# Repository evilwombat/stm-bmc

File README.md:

# Summary

## What is bubble memory?
[Bubble memory](https://en.wikipedia.org/wiki/Bubble_memory]) is an archaic (yet super awesome) type of nonvolatile computer memory. It stores data as a pattern of magnetization on the surface of a crystal, in a manner loosely similar to a magnetic hard drive. The amazing thing about bubble memory is that despite being magnetic in nature, it uses **no moving parts**. Unlike a magnetic hard drive, the storage medium stays in place, but the *data* moves along its surface. This is accomplished through some magical properties of the [crystal](https://en.wikipedia.org/wiki/Gadolinium_gallium_garnet) involved. Bubble memory was a promising new storage technology in the 70s and 80s, due to (at the time) impressive densities, though it was ultimately replaced by cheaper and more reliable flash memories. 

## What is this project?
This is a controller for Bubble Memory modules made by Texas Instruments in the 1980s. I have brought this up using TIB S0004 memory modules. This is a reasonably functional controller, capable of reading, erasing, and writing data, though some of the analog circuitry could probably use some refinement. This was a quarantine project so I had to start with what I had at the time.

## Demo videos (click to play)

PCB version: http://www.youtube.com/watch?v=yxEgAI12R1k

PCB (with explanation): http://www.youtube.com/watch?v=7U3c4cfQvKs

Original, breadboarded version: http://www.youtube.com/watch?v=vP2biZnxT7Y

Honestly, I can't believe the breadboard version even worked cleanly enough for bringup. Notice the sense amplifier on a separate PCB.

## Implementation

Since bubble memory modules lack an internal controller, a fair amount of external circuitry is needed to produce the carefully-timed constant-current pulses needed to run them, and to amplify/process the output of the bubble detector. Historically, the timing of the control pulses was generated by a pile of logic circuits, or by a microsequencer. Later, both Intel and TI released some ICs to assist with this. Although today these are largely unobtanium, some documentation survives, including an [early design document](Research/DevelcoReport.pdf) that predates the existence of the integrated controller. The discrete-transistor implementation of the function pulse generator (and the associated timing information) found in this document is what made this project possible.

In modern times, the digital portion of such a controller can be reasonably implemented using a regular microcontroller, in this case, an STM32F103. The state machine and timing logic is handled entirely in firmware, but a fair amount of external circuitry is still needed to convert the logic-level signals into coil drive pulses and/or constant-current "function" pulses that are fed into the bubble module itself.

The STM32 firmware implements the following:
* Bubble function timing generator (Generate/Annihilate/Transfer)
* Coil drive timing generator
* Major/minor loop state machine
* Basic loop tests, for bringup/tuning of the analog circuit
* Block I/O layer (with CRC and trivial block redundancy)
* UI layer (LCD, fonts, graphics, rotary encoder)
* Bootloader to actually load code from the bubble memory and run it
* Proof-of-concept payload that can be loaded and booted
* [Morning Music](https://www.youtube.com/watch?v=tEueYGq2mT4) (obviously)

Although historical documentation exists, most of the detailed information pertains to an earlier prototype of TI bubble memory (TBM0101), one that was ultimately not commercialized. In the more widely-available parts (such as TIB0203 and the TIB-S0004 used here), some of the key operating parameters (such as drive cycle timings and function timings) have changed substantially. The correct parameters needed to be determined partly by trial and error, and partly by translating some old Russian datasheets relating to their knockoffs of TI's more modern bubble memory parts.

## Hardware Gallery

Assembled PCB version:

Schematic:

PCB layout:

First breadboarded version:

Close-up up of the breadboarded analog section. The amplifier circuit is too sensitive for breadboarding, and was built on a piece of perf-board. An alternate amplifier design would be less sensitive to minor variations in detector resistance, and hence would not need to many trimpots. But this design would be more sensitive to noise (which was much harder to control in a setup like this).

Some of the first bubbles!

## What's with the music and countdown?

Perhaps the best-known example of a bubble memory design is Konami's famous [Bubble System](https://en.wikipedia.org/wiki/Bubble_System) arcade platform.

In 1985, Konami released a number of arcade machines that used bubble memory (rather than silicon ROM) for game storage. When switched on, these machines spoke a voice-based countdown while the memory modules were heated to their operating temperature. Since bubble memory is read slowly and sequentially, the game residing within was first copied into RAM before it could be executed; the machine displayed an [on-screen countdown](https://www.youtube.com/watch?v=mbM_YPyVJBE&t=175s) (and played an accompanying melody) during this process. The system was ultimately a commercial failure, because the bubble memory was expensive and very sensitive to external magnetic fields; meanwhile, silicon-based storage was growing cheaper. The few games that used this system were eventually re-released on ROM, but some original bubble-based systems survive to this day. 

<b>Fun fact:</b> The melody that played during the loading countdown was called the Morning Music, because it played every morning when the arcade operator switched on the machine. It has been said that the boot process was a kind of special / unusual thing to see, and that people would show up bright and early to the arcade just to watch the machines boot (and to listen to the morning music).

> Written with [StackEdit](https://stackedit.io/).

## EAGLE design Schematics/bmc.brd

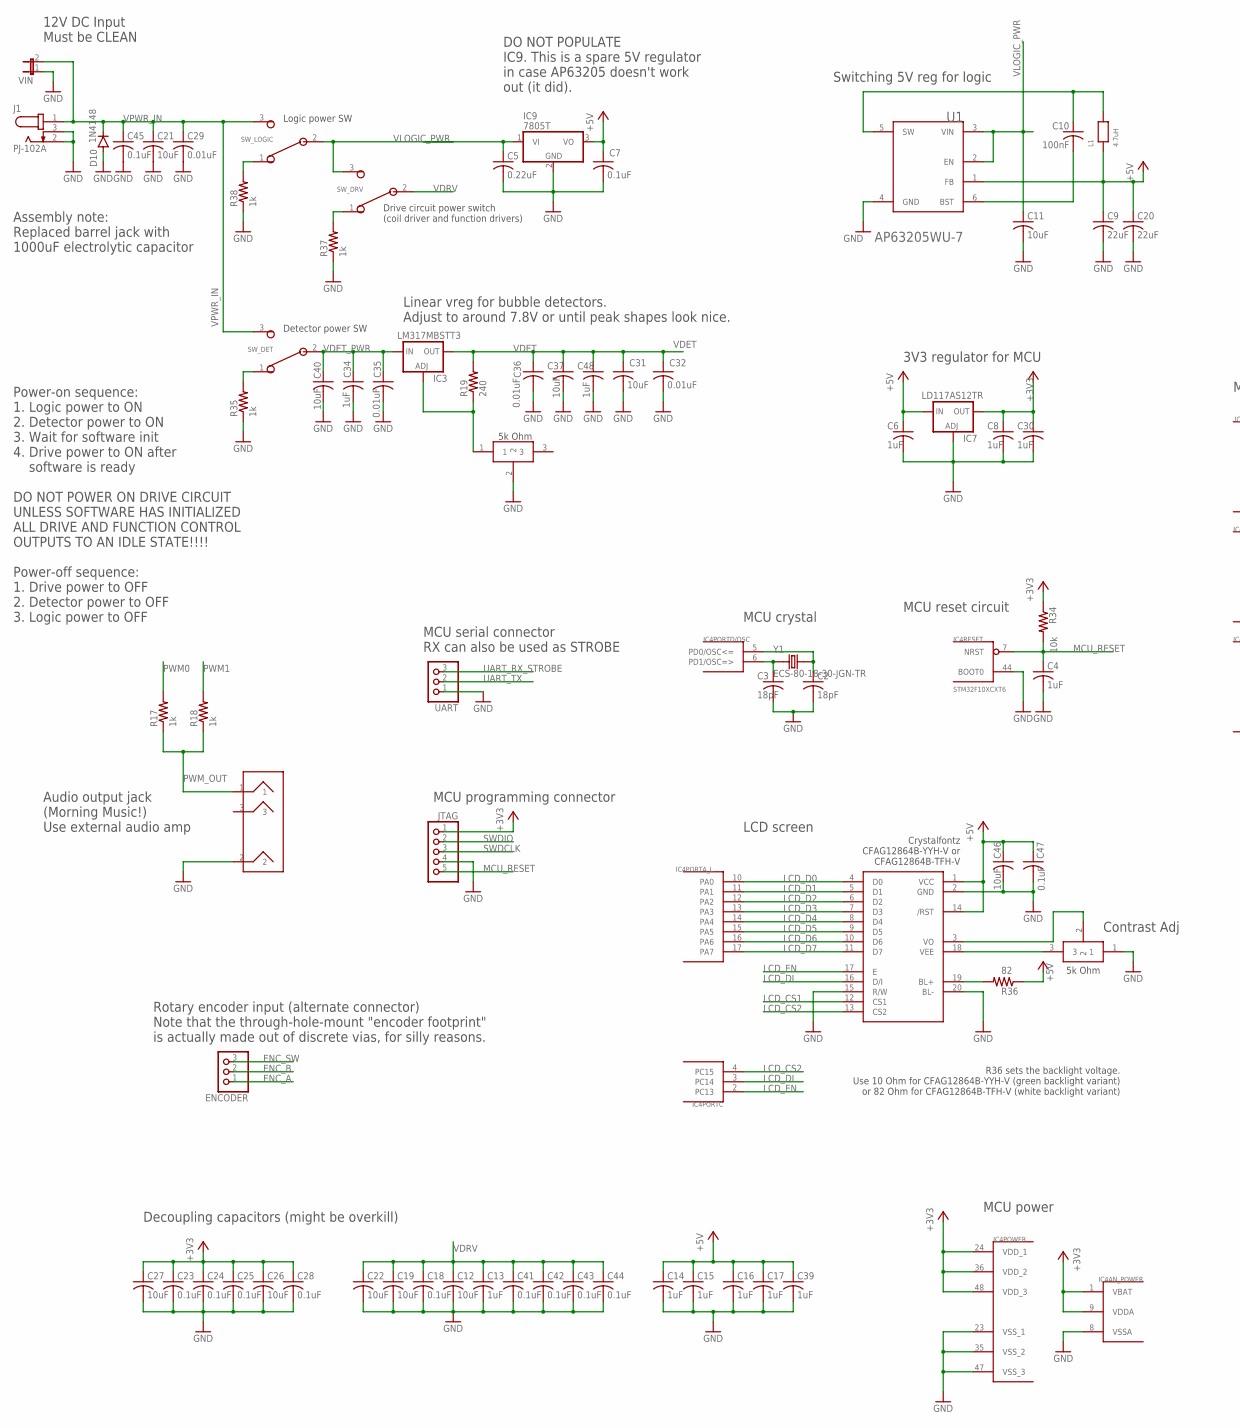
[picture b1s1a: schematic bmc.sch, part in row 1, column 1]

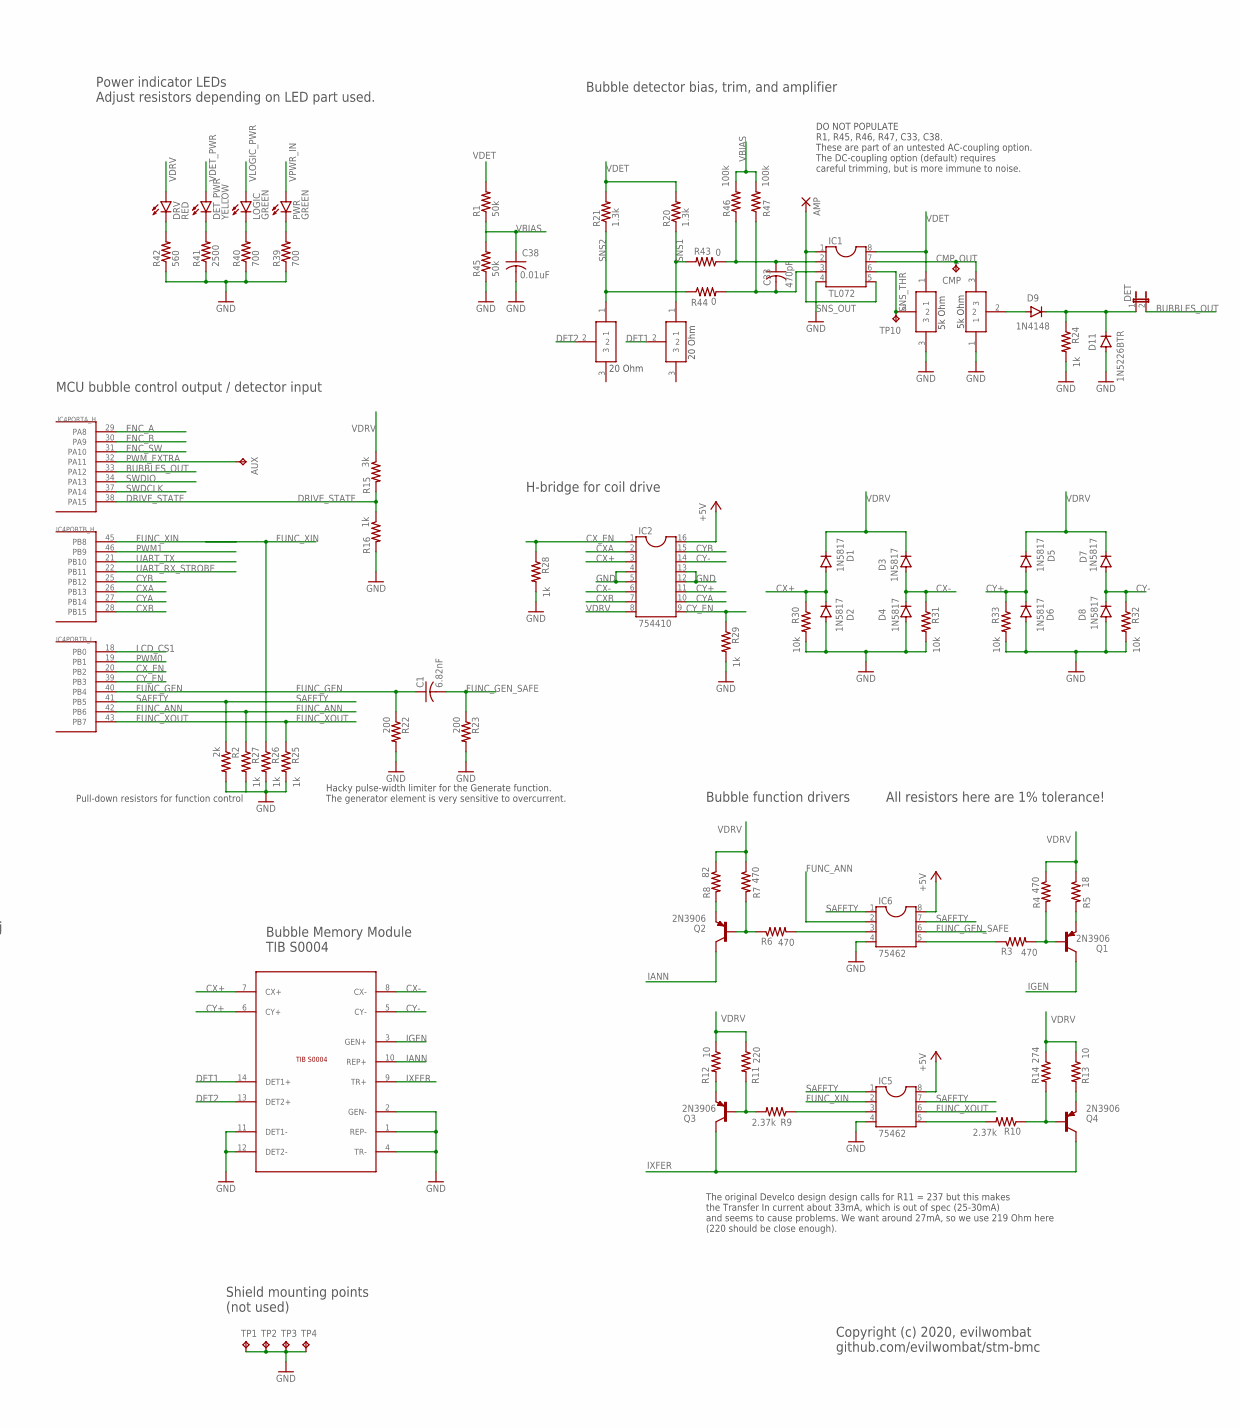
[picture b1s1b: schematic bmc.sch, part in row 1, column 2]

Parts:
AMP: 1,6/0,8
AUX: TPTP07R; TP07R
C1: 6.82nF; CAPC2012X110
C2, C3: 18pF; CAPC2012X110
C4, C6, C8, C13, C14, C15, C16, C17, C30, C34, C39, C48: 1uF; CAPC2012X110
C5: 0.22uF; CAPC2012X110
C7, C18, C41, C42, C43, C44, C45, C47: 0.1uF; CAPC2012X110
C9, C20: 22uF; CAPC2012X110
C10: 100nF; CAPC2012X110
C11, C12, C19, C21, C22, C31, C37, C40, C46: 10uF; CAPC3216X135
C23, C24, C25, C28: 0.1uF; CAPC1005X60
C26, C27: 10uF; CAPC2012X110
C29, C32, C35, C36, C38: 0.01uF; CAPC2012X110
C33: 470pF; CAPC2012X110
CMP: TPTP07R; TP07R
D1, D2, D3, D4, D5, D6, D7, D8: 1N5817; DO-41
D9, D10: 1N4148; DO-41
D11: 1N5226BTR; DO-41
DET: JP1E; JP1
DET_PWR: YELLOW; CHIPLED_1206
DISP1: CFAG12864B; CFAG16864B
DRV: RED; CHIPLED_1206
ENCODER: PINHD-1X3; 1X03
IC1: TL072; DIL08
IC2: 754410; DIL16
IC3: LM317MBSTT3; SOT223
IC4: STM32F10XCXT6; TQFP48
IC5, IC6: 75462; DIL08
IC7: LD117AS12TR; SOT223
IC9: 7805T; TO220H
J1: PJ-102A; CUI_PJ-102A
JTAG: PINHD-1X5; 1X05
L1: 4.7uH; WE-PMI_1008
LOGIC: GREEN; CHIPLED_1206
MUSIC_OUT: STX-3501-3N
OLVL: PV36W
PWR: GREEN; CHIPLED_1206
Q1, Q2, Q3, Q4: 2N3906; TO92
R1, R45: 50k; R0805
R2: 2k; R0805
R3, R4, R6, R7: 470; R0805
R5: 18; R0805
R8: 82; R0805
R9, R10: 2.37k; R0805
R11: 220; R0805
R12, R13: 10; R0805
R14: 274; R0805
R15: 3k; R0805
R16, R17, R18, R24, R25, R26, R27, R28, R29, R35, R37, R38: 1k; R0805
R19: 240; R0805
R20, R21: 1.3k; 0204/7
R22, R23: 200; R0805
R30, R31, R32, R33, R34: 10k; R0805
R36: 82; R1206
R39, R40: 700; R0805
R41: 2500; R0805
R42: 560; R0805
R43, R44: 0; R0805
R46, R47: 100k; R0805
SW_DET: SW_SPDT
SW_DRV: SW_SPDT
SW_LOGIC: SW_SPDT
THR: PV36W
TP1, TP2, TP3, TP4: TPTP20SQ; TP20SQ
TP10: TPTP07R; TP07R
TRIM+: PV36W
TRIM-: 20 Ohm; PV36W
U1: DIODES_INC._AP63205WU-7DIODES_INC._AP63205WU-7_0_3; DIODES_INC._AP63205WU-7_3
U$1: TP3386; 3386-EY5
U$5: TIB_S0004; MBM
UART: PINHD-1X3; 1X03
VDET: PV36W
VIN: JP1E; JP1
Y1: ECS-80-18-30-JGN-TR; XTAL_ECS-80-18-30-JGN-TR

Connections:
+3V3: C8.1, C23.1, C24.1, C25.1, C26.1, C27.1, C28.1, C30.1, IC4.1 (VBAT), IC4.9 (VDDA), IC4.24 (VDD_1), IC4.36 (VDD_2), IC4.48 (VDD_3), IC7.4 (OUT), JTAG.1, R34.1
+5V: C6.1, C7.1, C9.1, C14.1, C15.1, C16.1, C17.1, C20.1, C39.1, C46.1, C47.1, DISP1.1 (VCC), DISP1.14 (/RST), IC2.16, IC5.8, IC6.8, IC7.3 (IN), IC9.3 (VO), L1.1, R36.1, U1.1 (FB)
BUBBLES_OUT: DET.2, IC4.33 (PA12)
BUBBLES_OUT_JP: D9.C, D11.C, DET.1, R24.1
CMP_OUT: CMP.TP, IC1.7, OLVL.3
CX+: D1.A, D2.C, IC2.3, R30.1, U$5.7 (CX+)
CX-: D3.A, D4.C, IC2.6, R31.1, U$5.8 (CX-)
CXA: IC2.2, IC4.26 (PB13)
CXB: IC2.7, IC4.28 (PB15)
CX_EN: IC2.1, IC4.20 (PB2), R28.1
CY+: D5.A, D6.C, IC2.11, R33.1, U$5.6 (CY+)
CY-: D7.A, D8.C, IC2.14, R32.1, U$5.5 (CY-)
CYA: IC2.10, IC4.27 (PB14)
CYB: IC2.15, IC4.25 (PB12)
CY_EN: IC2.9, IC4.39 (PB3), R29.1
DET1: TRIM-.2, U$5.14 (DET1+)
DET2: TRIM+.2, U$5.13 (DET2+)
DRIVE_STATE: IC4.38 (PA15), R15.2, R16.1
ENC_A: ENCODER.1, IC4.29 (PA8)
ENC_B: ENCODER.2, IC4.30 (PA9)
ENC_SW: ENCODER.3, IC4.31 (PA10)
FUNC_ANN: IC4.42 (PB6), IC6.2, R27.1
FUNC_GEN: C1.1, IC4.40 (PB4), R22.1
FUNC_GEN_SAFE: C1.2, IC6.6, R23.1
FUNC_XIN: IC4.45 (PB8), IC5.2, R26.1
FUNC_XOUT: IC4.43 (PB7), IC5.6, R25.1
GND: C2.2, C3.2, C4.2, C5.2, C6.2, C7.2, C8.2, C9.2, C11.2, C12.2, C13.2, C14.2, C15.2, C16.2, C17.2, C18.2, C19.2, C20.2, C21.2, C22.2, C23.2, C24.2, C25.2, C26.2, C27.2, C28.2, C29.2, C30.2, C31.2, C32.2, C34.2, C35.2, C36.2, C37.2, C38.2, C39.2, C40.2, C41.2, C42.2, C43.2, C44.2, C45.2, C46.2, C47.2, C48.2, D2.A, D4.A, D6.A, D8.A, D10.A, D11.A, DISP1.2 (GND), DISP1.15 (R/W), DISP1.20 (BL-), IC1.4, IC2.4, IC2.5, IC2.12, IC2.13, IC4.8 (VSSA), IC4.23 (VSS_1), IC4.35 (VSS_2), IC4.44 (BOOT0), IC4.47 (VSS_3), IC5.4, IC6.4, IC7.1 (ADJ), IC9.2 (GND), J1.2, J1.3, JTAG.4, MUSIC_OUT.2, OLVL.1, R2.2, R16.2, R22.2, R23.2, R24.2, R25.2, R26.2, R27.2, R28.2, R29.2, R30.2, R31.2, R32.2, R33.2, R35.1, R37.1, R38.1, R39.1, R40.1, R41.1, R42.1, R45.1, THR.3, TP1.TP, TP2.TP, TP3.TP, TP4.TP, U1.4 (GND), U$1.1, U$5.1 (REP-), U$5.2 (GEN-), U$5.4 (TR-), U$5.11 (DET1-), U$5.12 (DET2-), UART.1, VDET.2, VIN.1
IANN: Q2.1 (C), U$5.10 (REP+)
IGEN: Q1.1 (C), U$5.3 (GEN+)
IXFER: Q3.1 (C), Q4.1 (C), U$5.9 (TR+)
LCD_BL+: DISP1.19 (BL+), R36.2
LCD_CS1: DISP1.12 (CS1), IC4.18 (PB0)
LCD_CS2: DISP1.13 (CS2), IC4.4 (PC15)
LCD_D0: DISP1.4 (D0), IC4.10 (PA0)
LCD_D1: DISP1.5 (D1), IC4.11 (PA1)
LCD_D2: DISP1.6 (D2), IC4.12 (PA2)
LCD_D3: DISP1.7 (D3), IC4.13 (PA3)
LCD_D4: DISP1.8 (D4), IC4.14 (PA4)
LCD_D5: DISP1.9 (D5), IC4.15 (PA5)
LCD_D6: DISP1.10 (D6), IC4.16 (PA6)
LCD_D7: DISP1.11 (D7), IC4.17 (PA7)
LCD_DI: DISP1.16 (D/I), IC4.3 (PC14)
LCD_EN: DISP1.17 (E), IC4.2 (PC13)
LCD_VEE: DISP1.18 (VEE), U$1.3
LCD_VO: DISP1.3 (VO), U$1.2
MCU_RESET: C4.1, IC4.7 (NRST), JTAG.5, R34.2
unnamed: C3.1, IC4.6 (PD1/OSC=>), Y1.1 (IN/OUT)
unnamed: C2.1, IC4.5 (PD0/OSC<=), Y1.2 (OUT/IN)
unnamed: D9.A, OLVL.2
unnamed: C33.2, IC1.3, R44.2, R47.1
unnamed: Q1.2 (B), R3.2, R4.2
unnamed: IC6.5, R3.1
unnamed: Q1.3 (E), R5.2
unnamed: IC6.3, R6.2
unnamed: Q2.2 (B), R6.1, R7.2
unnamed: IC5.3, R9.1
unnamed: Q2.3 (E), R8.2
unnamed: IC5.5, R10.2
unnamed: Q3.3 (E), R12.2
unnamed: Q3.2 (B), R9.2, R11.2
unnamed: Q4.2 (B), R10.1, R14.2
unnamed: Q4.3 (E), R13.2
unnamed: C33.1, IC1.2, R43.1, R46.1
unnamed: IC3.1 (ADJ), R19.1, VDET.1
unnamed: R35.2, SW_DET.1 (NC)
unnamed: R37.2, SW_DRV.1 (NC)
unnamed: R38.2, SW_LOGIC.1 (NC)
unnamed: C10.1, L1.2, U1.5 (SW)
unnamed: PWR.C, R39.2
unnamed: LOGIC.C, R40.2
unnamed: DET_PWR.C, R41.2
unnamed: DRV.C, R42.2
unnamed: C10.2, U1.6 (BST)
PWM0: IC4.19 (PB1), R17.2
PWM1: IC4.46 (PB9), R18.2
PWM_EXTRA: AUX.TP, IC4.32 (PA11)
PWM_OUT: MUSIC_OUT.1, R17.1, R18.1
SAFETY: IC4.41 (PB5), IC5.1, IC5.7, IC6.1, IC6.7, R2.1
SNS1: R20.1, R43.2, TRIM-.1
SNS2: R21.1, R44.1, TRIM+.1
SNS_OUT: AMP.1, IC1.1, IC1.5
SNS_THR: IC1.6, THR.2, TP10.TP
SWDCLK: IC4.37 (PA14), JTAG.3
SWDIO: IC4.34 (PA13), JTAG.2
UART_RX_STROBE: IC4.22 (PB11), UART.3
UART_TX: IC4.21 (PB10), UART.2
VBIAS: C38.1, R1.1, R45.2, R46.2, R47.2
VDET: C31.1, C32.1, C36.1, C37.1, C48.1, IC1.8, IC3.2 (OUT), IC3.4 (OUT), R1.2, R19.2, R20.2, R21.2, THR.1
VDET_PWR: C34.1, C35.1, C40.1, DET_PWR.A, IC3.3 (IN), SW_DET.2 (COM)
VDRV: C12.1, C13.1, C18.1, C19.1, C22.1, C41.1, C42.1, C43.1, C44.1, D1.C, D3.C, D5.C, D7.C, DRV.A, IC2.8, R4.1, R5.1, R7.1, R8.1, R11.1, R12.1, R13.1, R14.1, R15.1, SW_DRV.2 (COM)
VLOGIC_PWR: C5.1, C11.1, IC9.1 (VI), LOGIC.A, SW_DRV.3 (NO), SW_LOGIC.2 (COM), U1.2 (EN), U1.3 (VIN)
VPWR_IN: C21.1, C29.1, C45.1, D10.C, J1.1, PWR.A, SW_DET.3 (NO), SW_LOGIC.3 (NO), VIN.2

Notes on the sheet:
The original Develco design design calls for R11 = 237 but this makes the Transfer In current about 33mA, which is out of spec (25-30mA) and seems to cause problems. We want around 27mA, so we use 219 Ohm here (220 should be close enough).
DO NOT POPULATE R1, R45, R46, R47, C33, C38. These are part of an untested AC-coupling option. The DC-coupling option (default) requires careful trimming, but is more immune to noise.
5k Ohm
20 Ohm
DO NOT POPULATE IC9. This is a spare 5V regulator in case AP63205 doesn't work out (it did).
Switching 5V reg for logic
3V3 regulator for MCU
Linear vreg for bubble detectors. Adjust to around 7.8V or until peak shapes look nice.
Logic power SW
Detector power SW
Drive circuit power switch (coil driver and function drivers)
12V DC Input Must be CLEAN
Power indicator LEDs Adjust resistors depending on LED part used.
Audio output jack (Morning Music!) Use external audio amp
MCU serial connector RX can also be used as STROBE
MCU programming connector
MCU crystal
Rotary encoder input (alternate connector) Note that the through-hole-mount "encoder footprint" is actually made out of discrete vias, for silly reasons.
Decoupling capacitors (might be overkill)
LCD screen
Contrast Adj
Crystalfontz CFAG12864B-YYH-V or CFAG12864B-TFH-V
R36 sets the backlight voltage. Use 10 Ohm for CFAG12864B-YYH-V (green backlight variant) or 82 Ohm for CFAG12864B-TFH-V (white backlight variant)
Bubble detector bias, trim, and amplifier
Hacky pulse-width limiter for the Generate function. The generator element is very sensitive to overcurrent.
Pull-down resistors for function control
MCU bubble control output / detector input
MCU reset circuit
MCU power
H-bridge for coil drive
Bubble Memory Module TIB S0004
Bubble function drivers
Shield mounting points (not used)
All resistors here are 1% tolerance!
Assembly note: Replaced barrel jack with 1000uF electrolytic capacitor
Power-on sequence: 1. Logic power to ON 2. Detector power to ON 3. Wait for software init 4. Drive power to ON after software is ready DO NOT POWER ON DRIVE CIRCUIT UNLESS SOFTWARE HAS INITIALIZED ALL DRIVE AND FUNCTION CONTROL OUTPUTS TO AN IDLE STATE!!!! Power-off sequence: 1. Drive power to OFF 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
Copyright (c) 2020, evilwombat github.com/evilwombat/stm-bmc

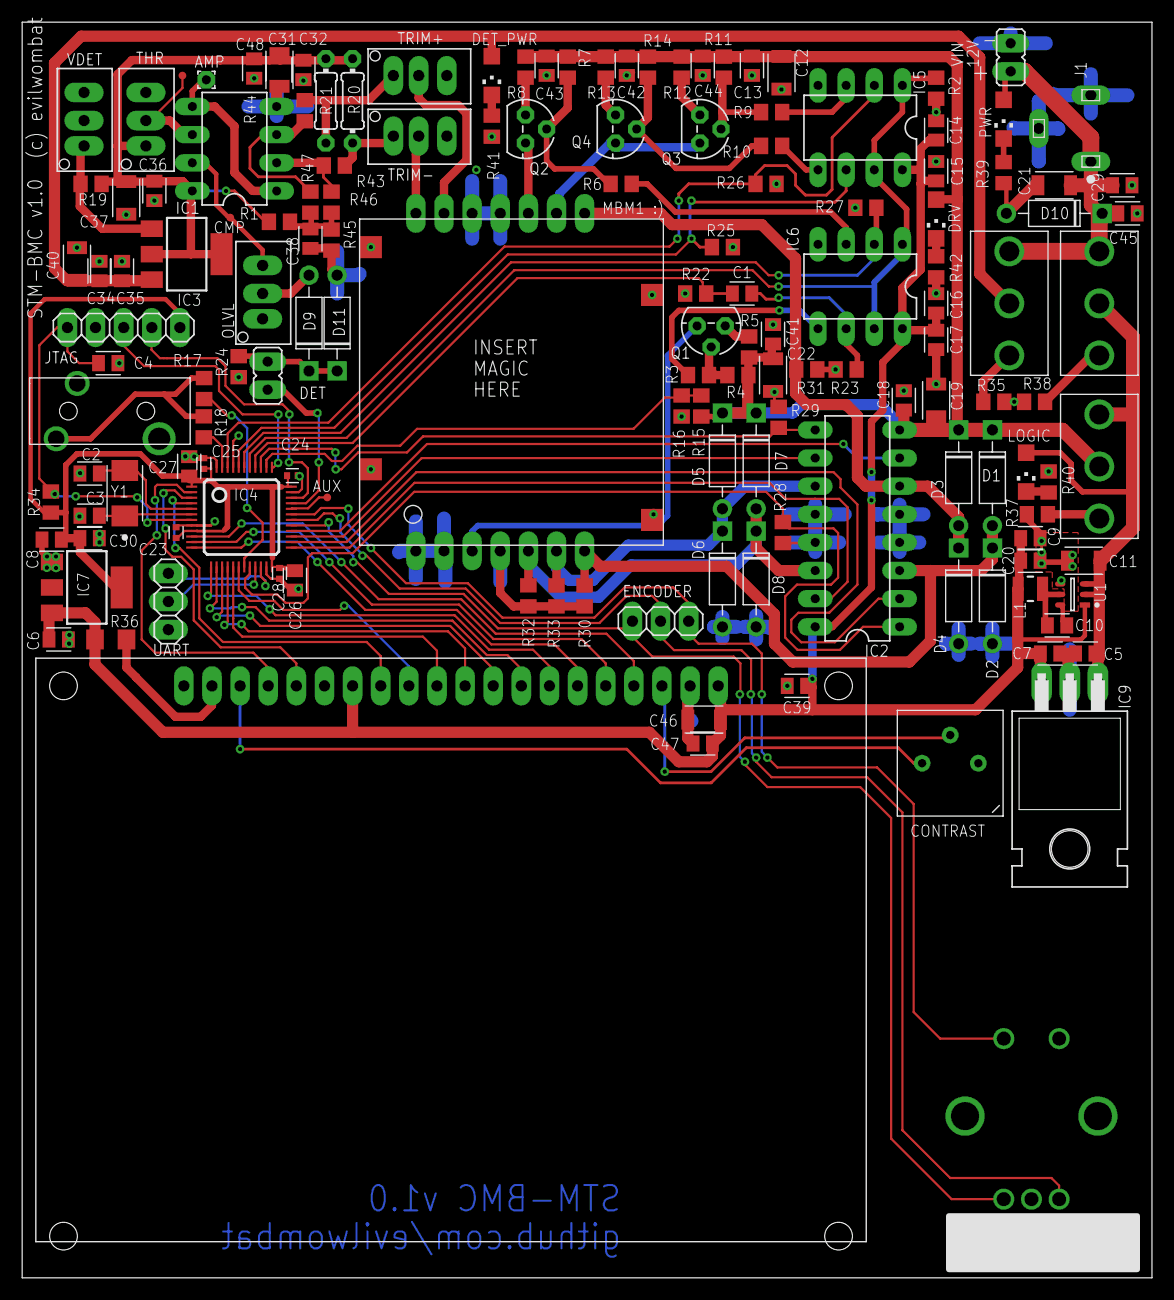
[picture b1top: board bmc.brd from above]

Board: 2 copper layers, 102.0 x 113.4 mm, 151 parts (1 on the bottom side), 92 nets.

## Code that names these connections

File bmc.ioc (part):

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Mcu.Name=STM32F103C(8-B)Tx
Mcu.Package=LQFP48
Mcu.UserName=STM32F103C8Tx
PA10.GPIOParameters=GPIO_PuPd,GPIO_Label
PA10.GPIO_Label=ENC_BUTTON
PA10.GPIO_PuPd=GPIO_PULLUP
PA10.Signal=GPIO_Input
PA12.GPIOParameters=GPIO_Label
PA12.GPIO_Label=BUBBLE_DETECT
PA12.Signal=GPXTI12
PA15.GPIOParameters=GPIO_PuPd,GPIO_Label
PA15.GPIO_Label=DRIVE_STATE
PA15.GPIO_PuPd=GPIO_PULLUP
PA15.Signal=GPIO_Input
PA8.GPIOParameters=GPIO_PuPd,GPIO_Label
PA8.GPIO_Label=ENC_A
PA8.GPIO_PuPd=GPIO_PULLUP
PA8.Signal=S_TIM1_CH1
PA9.GPIOParameters=GPIO_PuPd,GPIO_Label
PA9.GPIO_Label=ENC_B
PA9.GPIO_PuPd=GPIO_PULLUP
PA9.Signal=S_TIM1_CH2
PB0.GPIOParameters=GPIO_Speed,PinState,GPIO_PuPd,GPIO_Label
PB0.GPIO_Label=SAFETY
PB0.GPIO_PuPd=GPIO_PULLUP
PB0.GPIO_Speed=GPIO_SPEED_FREQ_HIGH
PB0.PinState=GPIO_PIN_SET
PB0.Signal=GPIO_Output
PB1.Signal=S_TIM3_CH4
PB10.Mode=Half_duplex(single_wire_mode)
PB10.Signal=USART3_TX
PB11.GPIOParameters=GPIO_Speed,GPIO_Label
PB11.GPIO_Label=STROBE
PB11.GPIO_Speed=GPIO_SPEED_FREQ_HIGH
PB11.Signal=GPIO_Output
PB12.GPIOParameters=GPIO_Speed,GPIO_Label
PB12.GPIO_Label=FUNC_XOUT
PB12.GPIO_Speed=GPIO_SPEED_FREQ_HIGH
PB12.Signal=GPIO_Output
PB13.GPIOParameters=GPIO_Speed,GPIO_Label
PB13.GPIO_Label=FUNC_XIN
PB13.GPIO_Speed=GPIO_SPEED_FREQ_HIGH
PB13.Signal=GPIO_Output
PB14.GPIOParameters=GPIO_Speed,GPIO_Label
PB14.GPIO_Label=FUNC_GEN
PB14.GPIO_Speed=GPIO_SPEED_FREQ_HIGH
PB14.Signal=GPIO_Output
PB15.GPIOParameters=GPIO_Speed,GPIO_Label
PB15.GPIO_Label=FUNC_ANN
PB15.GPIO_Speed=GPIO_SPEED_FREQ_HIGH
PB15.Signal=GPIO_Output
PB3.GPIOParameters=GPIO_Speed,GPIO_Label
PB3.GPIO_Label=DRV_A1
PB3.GPIO_Speed=GPIO_SPEED_FREQ_HIGH
PB3.Signal=GPIO_Output
PB4.GPIOParameters=GPIO_Speed,GPIO_Label
PB4.GPIO_Label=DRV_A2
PB4.GPIO_Speed=GPIO_SPEED_FREQ_HIGH
PB4.Signal=GPIO_Output
PB5.GPIOParameters=GPIO_Speed,GPIO_Label
PB5.GPIO_Label=DRV_A3
PB5.GPIO_Speed=GPIO_SPEED_FREQ_HIGH
PB5.Signal=GPIO_Output
PB6.GPIOParameters=GPIO_Speed,GPIO_Label
PB6.GPIO_Label=DRV_A4
PB6.GPIO_Speed=GPIO_SPEED_FREQ_HIGH
PB6.Signal=GPIO_Output
PB7.GPIOParameters=GPIO_Speed,GPIO_Label
PB7.GPIO_Label=DRV_EN_12
PB7.GPIO_Speed=GPIO_SPEED_FREQ_HIGH
PB7.Signal=GPIO_Output
PB8.GPIOParameters=GPIO_Speed,PinState,GPIO_PuPd,GPIO_Label
PB8.GPIO_Label=DRV_EN_34
PB8.GPIO_PuPd=GPIO_NOPULL
PB8.GPIO_Speed=GPIO_SPEED_FREQ_HIGH
PB8.PinState=GPIO_PIN_RESET
PB8.Signal=GPIO_Output
PB9.Signal=S_TIM4_CH4
PD0-OSC_IN.Mode=HSE-External-Oscillator
PD0-OSC_IN.Signal=RCC_OSC_IN
PD1-OSC_OUT.Mode=HSE-External-Oscillator
PD1-OSC_OUT.Signal=RCC_OSC_OUT
RCC.SYSCLKFreq_VALUE=72000000
RCC.SYSCLKSource=RCC_SYSCLKSOURCE_PLLCLK
board=custom

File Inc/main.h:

/* USER CODE BEGIN Header */
/**
  ******************************************************************************
  * @file           : main.h
  * @brief          : Header for main.c file.
  *                   This file contains the common defines of the application.
  ******************************************************************************
  ** This notice applies to any and all portions of this file
  * that are not between comment pairs USER CODE BEGIN and
  * USER CODE END. Other portions of this file, whether 
  * inserted by the user or by software development tools
  * are owned by their respective copyright owners.
  *
  * COPYRIGHT(c) 2020 STMicroelectronics
  *
  * Redistribution and use in source and binary forms, with or without modification,
  * are permitted provided that the following conditions are met:
  *   1. Redistributions of source code must retain the above copyright notice,
  *      this list of conditions and the following disclaimer.
  *   2. Redistributions in binary form must reproduce the above copyright notice,
  *      this list of conditions and the following disclaimer in the documentation
  *      and/or other materials provided with the distribution.
  *   3. Neither the name of STMicroelectronics nor the names of its contributors
  *      may be used to endorse or promote products derived from this software
  *      without specific prior written permission.
  *
  * THIS SOFTWARE IS PROVIDED BY THE COPYRIGHT HOLDERS AND CONTRIBUTORS "AS IS"
  * AND ANY EXPRESS OR IMPLIED WARRANTIES, INCLUDING, BUT NOT LIMITED TO, THE
  * IMPLIED WARRANTIES OF MERCHANTABILITY AND FITNESS FOR A PARTICULAR PURPOSE ARE
  * DISCLAIMED. IN NO EVENT SHALL THE COPYRIGHT HOLDER OR CONTRIBUTORS BE LIABLE
  * FOR ANY DIRECT, INDIRECT, INCIDENTAL, SPECIAL, EXEMPLARY, OR CONSEQUENTIAL
  * DAMAGES (INCLUDING, BUT NOT LIMITED TO, PROCUREMENT OF SUBSTITUTE GOODS OR
  * SERVICES; LOSS OF USE, DATA, OR PROFITS; OR BUSINESS INTERRUPTION) HOWEVER
  * CAUSED AND ON ANY THEORY OF LIABILITY, WHETHER IN CONTRACT, STRICT LIABILITY,
  * OR TORT (INCLUDING NEGLIGENCE OR OTHERWISE) ARISING IN ANY WAY OUT OF THE USE
  * OF THIS SOFTWARE, EVEN IF ADVISED OF THE POSSIBILITY OF SUCH DAMAGE.
  *
  ******************************************************************************
  */
/* USER CODE END Header */

/* Define to prevent recursive inclusion -------------------------------------*/
#ifndef __MAIN_H
#define __MAIN_H

#ifdef __cplusplus
extern "C" {
#endif

/* Includes ------------------------------------------------------------------*/
#include "stm32f1xx_hal.h"

/* Private includes ----------------------------------------------------------*/
/* USER CODE BEGIN Includes */

/* USER CODE END Includes */

/* Exported types ------------------------------------------------------------*/
/* USER CODE BEGIN ET */

/* USER CODE END ET */

/* Exported constants --------------------------------------------------------*/
/* USER CODE BEGIN EC */

/* USER CODE END EC */

/* Exported macro ------------------------------------------------------------*/
/* USER CODE BEGIN EM */

/* USER CODE END EM */

void HAL_TIM_MspPostInit(TIM_HandleTypeDef *htim);

/* Exported functions prototypes ---------------------------------------------*/
void Error_Handler(void);

/* USER CODE BEGIN EFP */

/* USER CODE END EFP */

/* Private defines -----------------------------------------------------------*/
#define LCD_DI_Pin GPIO_PIN_13
#define LCD_DI_GPIO_Port GPIOC
#define LCD_CS2_Pin GPIO_PIN_14
#define LCD_CS2_GPIO_Port GPIOC
#define LCD_CS1_Pin GPIO_PIN_15
#define LCD_CS1_GPIO_Port GPIOC
#define LCD_D0_Pin GPIO_PIN_0
#define LCD_D0_GPIO_Port GPIOA
#define LCD_D1_Pin GPIO_PIN_1
#define LCD_D1_GPIO_Port GPIOA
#define LCD_D2_Pin GPIO_PIN_2
#define LCD_D2_GPIO_Port GPIOA
#define LCD_D3_Pin GPIO_PIN_3
#define LCD_D3_GPIO_Port GPIOA
#define LCD_D4_Pin GPIO_PIN_4
#define LCD_D4_GPIO_Port GPIOA
#define LCD_D5_Pin GPIO_PIN_5
#define LCD_D5_GPIO_Port GPIOA
#define LCD_D6_Pin GPIO_PIN_6
#define LCD_D6_GPIO_Port GPIOA
#define LCD_D7_Pin GPIO_PIN_7
#define LCD_D7_GPIO_Port GPIOA
#define SAFETY_Pin GPIO_PIN_0
#define SAFETY_GPIO_Port GPIOB
#define LCD_E_Pin GPIO_PIN_2
#define LCD_E_GPIO_Port GPIOB
#define STROBE_Pin GPIO_PIN_11
#define STROBE_GPIO_Port GPIOB
#define FUNC_XOUT_Pin GPIO_PIN_12
#define FUNC_XOUT_GPIO_Port GPIOB
#define FUNC_XIN_Pin GPIO_PIN_13
#define FUNC_XIN_GPIO_Port GPIOB
#define FUNC_GEN_Pin GPIO_PIN_14
#define FUNC_GEN_GPIO_Port GPIOB
#define FUNC_ANN_Pin GPIO_PIN_15
#define FUNC_ANN_GPIO_Port GPIOB
#define ENC_A_Pin GPIO_PIN_8
#define ENC_A_GPIO_Port GPIOA
#define ENC_B_Pin GPIO_PIN_9
#define ENC_B_GPIO_Port GPIOA
#define ENC_BUTTON_Pin GPIO_PIN_10
#define ENC_BUTTON_GPIO_Port GPIOA
#define BUBBLE_DETECT_Pin GPIO_PIN_12
#define BUBBLE_DETECT_GPIO_Port GPIOA
#define DRIVE_STATE_Pin GPIO_PIN_15
#define DRIVE_STATE_GPIO_Port GPIOA
#define DRV_A1_Pin GPIO_PIN_3
#define DRV_A1_GPIO_Port GPIOB
#define DRV_A2_Pin GPIO_PIN_4
#define DRV_A2_GPIO_Port GPIOB
#define DRV_A3_Pin GPIO_PIN_5
#define DRV_A3_GPIO_Port GPIOB
#define DRV_A4_Pin GPIO_PIN_6
#define DRV_A4_GPIO_Port GPIOB
#define DRV_EN_12_Pin GPIO_PIN_7
#define DRV_EN_12_GPIO_Port GPIOB
#define DRV_EN_34_Pin GPIO_PIN_8
#define DRV_EN_34_GPIO_Port GPIOB
/* USER CODE BEGIN Private defines */

/* USER CODE END Private defines */

#ifdef __cplusplus
}
#endif

#endif /* __MAIN_H */

/************************ (C) COPYRIGHT STMicroelectronics *****END OF FILE****/

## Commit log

2020-12-13 Initial contribution
2020-12-13 Align with transfer gates, hopefully.
2020-12-13 test: Add more test patterns
2020-12-13 Switch to EXTI-based detection
    This frees up a timer
2020-12-13 Implement basic step counting
2020-12-13 Sort of kind of can read/write
2020-12-13 Get rid of the transfer fudge factor
2020-12-13 Transfer function and power state
2020-12-13 Free up TIM1
2020-12-13 Define XIN / XOUT signals
2020-12-13 control: Move some pins around for easier access
2020-12-13 Read/write, but timings are still kinda fucked??
2020-12-13 Wait for drive on startup
2020-12-13 Add transfer tests, which don't seem to do what I want
2020-12-13 Further fudge the transfer timings
2020-12-13 Oh fucking hell. Transfer timings.
2020-12-13 bmc: First bubbles!
2020-12-13 Check in the CubeMX project
2020-12-13 read: Take detector track length into account
2020-12-13 uart: Deal with newlines
2020-12-13 gpio: Move drive safety and clean up GPIOs
2020-12-13 music: Check in the score and converter
2020-12-13 Intial music!
2020-12-13 music: Add the music player too
2020-12-13 Initial music (uncompressed)
2020-12-13 Dump more stuff when writing
2020-12-13 HACK: Write 128 / read 128
2020-12-13 ui: Add LCD / Console
2020-12-13 Clean up a few warnings
2020-12-13 Add basic sector I/O
2020-12-13 HACK: re-read after reading
2020-12-13 Do the pinswap (still need to do B2)
2020-12-13 Show a pretty warmup screen
2020-12-13 Clear newlines on position change
2020-12-13 Tweak some timings
2020-12-13 Countdown!
2020-12-13 Fix font
2020-12-13 Switch to active-high function driver logic
    And fuck with timings accordingly.
2020-12-13 bmc: Update defect map
2020-12-13 Moar better error reporting
2020-12-13 Add a loader
2020-12-13 Move to UART2, to free up Timer1
2020-12-13 bmc: Clean up coil drive pulse generation
2020-12-13 block_io: Reduce sector redundancy
    Reduce redundancy a little, to make room for Tetris
2020-12-13 Make block_write use const pointer
2020-12-13 Clean up loading message
2020-12-13 Initial working payload
2020-12-13 bmc: Disable/enable interrupts during sequence runs
2020-12-13 music: Add the unaltered MIDI version
2020-12-13 Move to UART3
    This allows A0-A7 to be open
2020-12-13 bmc: Tweak transfer timings slightly
2020-12-13 Fix output formatting
2020-12-13 Moar purging in testing
2020-12-13 drivers: Add encoder
    Add a basic rotary encoder driver.
2020-12-13 Retry the transfer operation
    Sometimes, transfer will fail, but we can read the failed
    sector twice, to transfer out the stragglers and OR them
    wit the bubbles we transferred out the first time.
2020-12-13 payload: Switch to back to Snake
    This reverts commit e15a9e2b4ee967067b3f27bd34477ae7714afe13.
2020-12-13 block_io: Implement retries at the block write layer
2020-12-13 boot: Allow drive to be armed in menu
2020-12-13 Clean up menu
2020-12-13 main: Stop messing with interrupts
2020-12-13 Let's draw some blocky digits
2020-12-13 music: Code cleanup
2020-12-13 music: Make music interrupt-driven
2020-12-13 Bump seq length. Is the EXTI signal getting delayed?
2020-12-13 Drop attic and improve test output
2020-12-13 Integrate block read test and UI, sort of
2020-12-13 bmc: Add alternative defective loop map
    Add a defective loop map for an alternative bubble memory
    module that I have.
2020-12-13 Add pset
2020-12-13 Add raw read/write sector APIs
2020-12-13 gfx: Add a main menu
    Add a top-level menu for the entire device.
2020-12-13 bmc: Begin code cleanup
2020-12-13 Add payload header and CRC
2020-12-13 Bump sector redundancy
2020-12-13 Minor cosmetic changes
2020-12-13 Implement block I/O with error fallback
2020-12-13 bmc: Documentation / code cleanup
2020-12-13 Show information on startup
2020-12-13 payload: Switch to Tetris
2020-12-13 bmc: Minor code cleanup
2020-12-13 Add a hacky warmup sequence
2020-12-13 general: Remove dead code and improve documentation
2020-12-13 Move detector to A11 because fucking hell
    Fucking hell.
2020-12-13 Reconfigure pins for actual PCB
2020-12-13 Don't seek after every operation?
2020-12-13 app_main cleanup
2020-12-13 Fix off-by-one minor loop bug
2020-12-13 gfx: Clean up the graphics routines a bit
2020-12-13 font: Clean up font definition
2020-12-13 Refactor low-level block I/O
2020-12-13 Warm up the drive coils before anything else
2020-12-13 Selftest and other cleanup
2020-12-13 tests: Show more detailed test info
2020-12-13 Reduce cycle time if not reading
2020-12-13 doc: Add datasheets for selected components
2020-12-13 doc: Add historical documentation
    Add the historical documentation that was used to determine
    how to actually control the bubble memory module. This was
    scattered over the internet, in obscure archives. Without
    this documentation, this project would not have been
    possible. By gathering it in one place, I hope to help the
    next person who decides to play with these devices.
2020-12-13 design: Check in schematics / layout / gerbers
    Check in the hardware design files for the final board,
    along with PNGs of the schematic and layout. This version
    differs very slightly from the v1.0 that was manufactured,
    in that some silkscreen elements were slightly tweaked.
2022-02-24 doc: Add photos for documentation
    Add some photos of the project at various build stages.
2022-02-24 doc: Update README
    Add some more background information to the readme.
